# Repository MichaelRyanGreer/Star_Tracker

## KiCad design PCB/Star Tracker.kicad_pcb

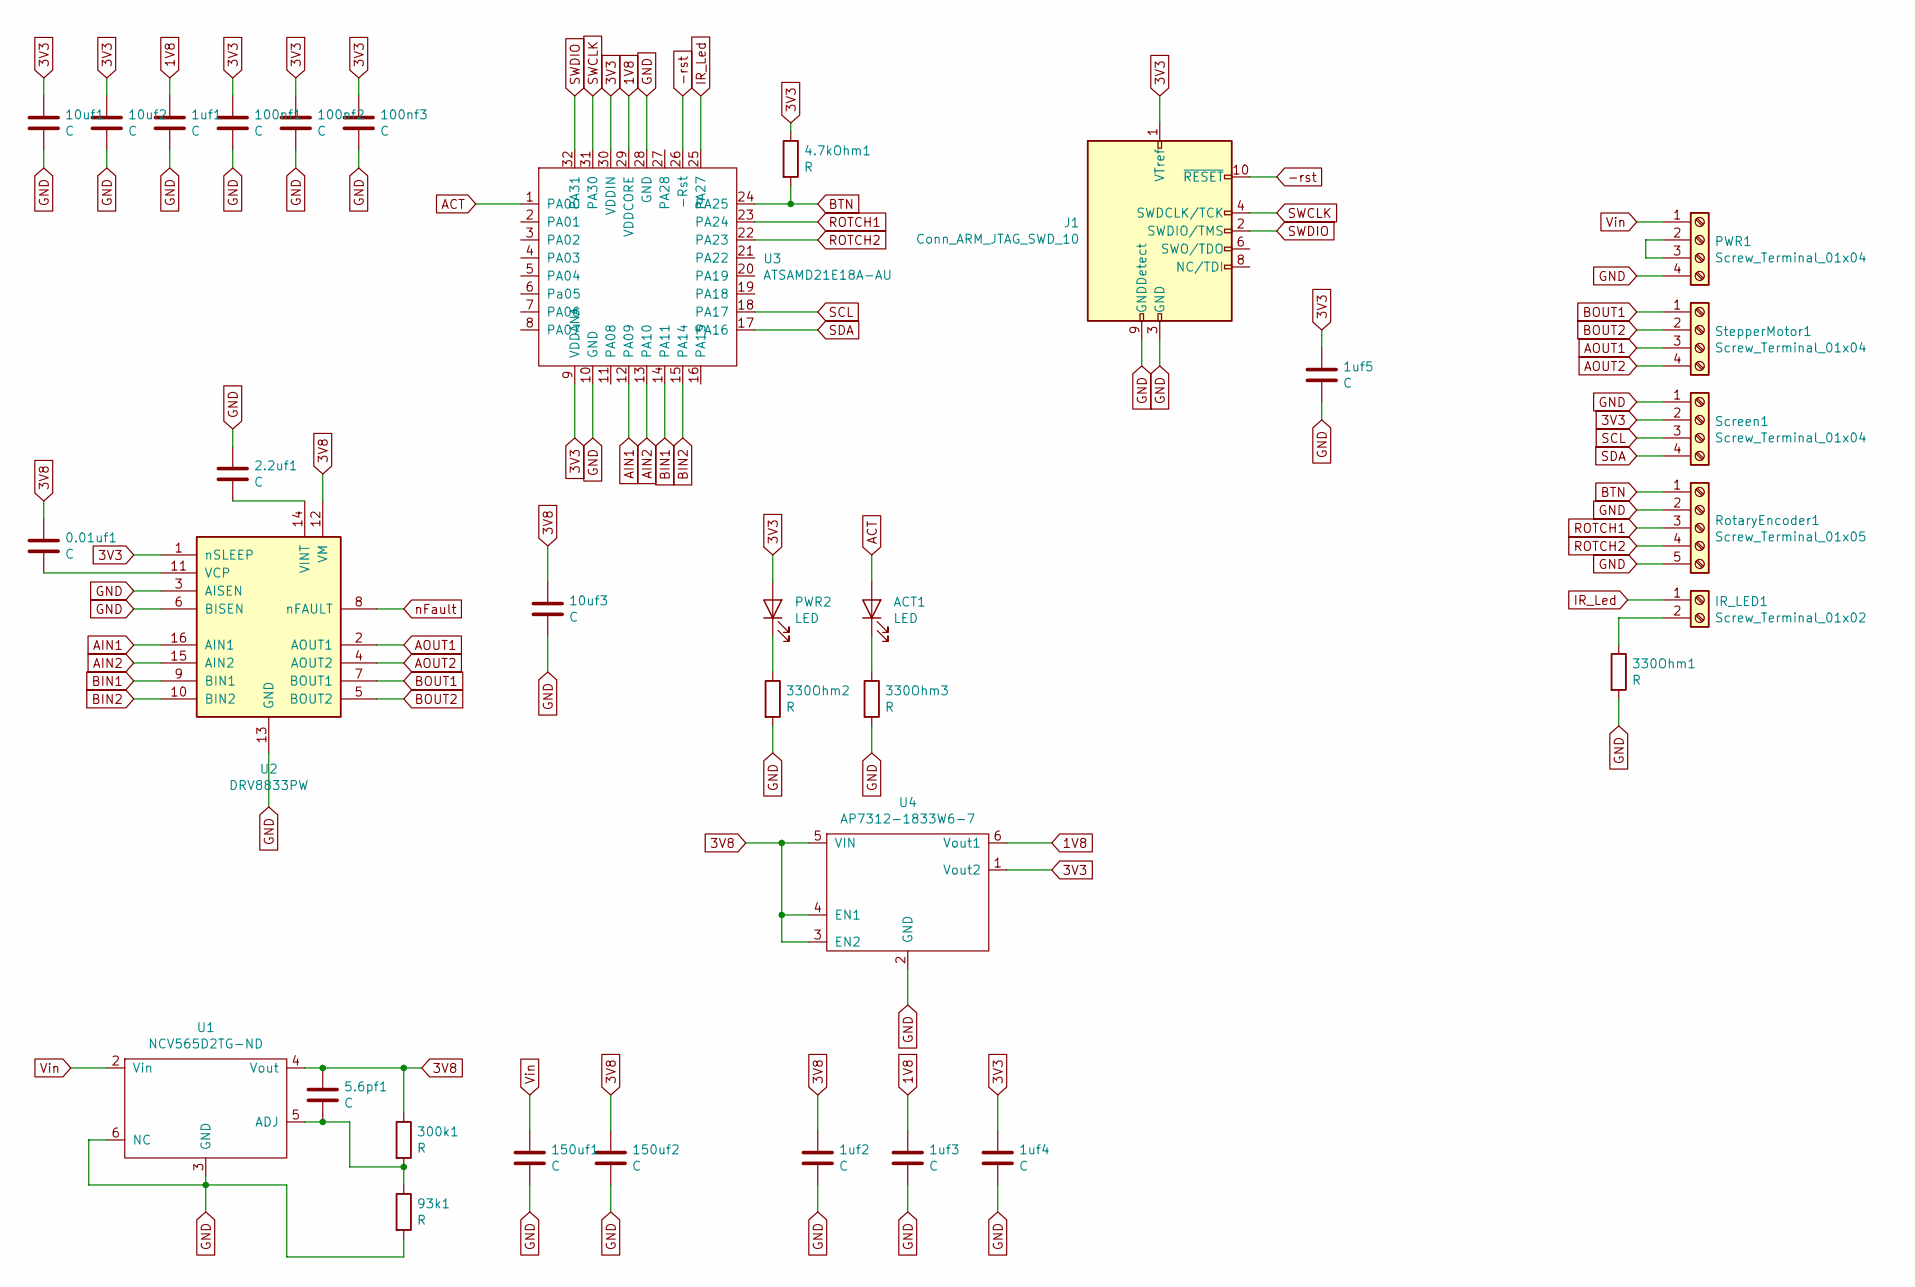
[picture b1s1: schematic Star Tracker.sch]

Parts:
0.01uf1, 1uf1, 1uf2, 1uf3, 1uf4, 1uf5, 2.2uf1, 5.6pf1, 10uf1, 10uf2, 10uf3, 100nf1, 100nf2, 100nf3, 150uf1, 150uf2: C; C_1206_3216Metric_Pad1.42x1.75mm_HandSolder
4.7kOhm1, 93k1, 300k1, 330Ohm1, 330Ohm2, 330Ohm3: R; R_1206_3216Metric_Pad1.42x1.75mm_HandSolder
ACT1: LED; D_1206_3216Metric_Pad1.42x1.75mm_HandSolder
IR_LED1: Screw_Terminal_01x02; PhoenixContact_MC_1,5_2-G-3.5_1x02_P3.50mm_Horizontal
J1: Conn_ARM_JTAG_SWD_10; PinHeader_2x05_P1.27mm_Vertical_SMD
PWR1: Screw_Terminal_01x04; PhoenixContact_MC_1,5_4-G-3.5_1x04_P3.50mm_Horizontal
PWR2: LED; D_1206_3216Metric_Pad1.42x1.75mm_HandSolder
RotaryEncoder1: Screw_Terminal_01x05; PhoenixContact_MC_1,5_5-G-3.5_1x05_P3.50mm_Horizontal
Screen1: Screw_Terminal_01x04; PhoenixContact_MC_1,5_4-G-3.5_1x04_P3.50mm_Horizontal
StepperMotor1: Screw_Terminal_01x04; PhoenixContact_MC_1,5_4-G-3.5_1x04_P3.50mm_Horizontal
U1: NCV565D2TG-ND; TO-263-5_TabPin6
U2: DRV8833PW; TSSOP-16_4.4x5mm_P0.65mm
U3: ATSAMD21E18A-AU; TQFP-32_7x7mm_P0.8mm
U4: AP7312-1833W6-7; SOT-23-6_Handsoldering

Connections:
1V8: 1uf1.1, 1uf3.1, U3.29 (VDDCORE), U4.6 (Vout1)
3V3: 1uf4.1, 1uf5.1, 4.7kOhm1.1, 10uf1.1, 10uf2.1, 100nf1.1, 100nf2.1, 100nf3.1, J1.1 (VTref), PWR2.2 (A), Screen1.2, U2.1 (nSLEEP), U3.9 (VDDANA), U3.30 (VDDIN), U4.1 (Vout2)
3V8: 0.01uf1.1, 1uf2.1, 5.6pf1.1, 10uf3.1, 150uf2.1, 300k1.1, U1.4 (Vout), U2.12 (VM), U4.3 (EN2), U4.4 (EN1), U4.5 (VIN)
-rst: J1.10 (~RESET~), U3.26 (-Rst)
ACT: ACT1.2 (A), U3.1 (PA00)
AIN1: U2.16 (AIN1), U3.12 (PA09)
AIN2: U2.15 (AIN2), U3.13 (PA10)
AOUT1: StepperMotor1.3, U2.2 (AOUT1)
AOUT2: StepperMotor1.4, U2.4 (AOUT2)
BIN1: U2.9 (BIN1), U3.14 (PA11)
BIN2: U2.10 (BIN2), U3.15 (PA14)
BOUT1: StepperMotor1.1, U2.7 (BOUT1)
BOUT2: StepperMotor1.2, U2.5 (BOUT2)
BTN: 4.7kOhm1.2, RotaryEncoder1.1, U3.24 (PA25)
GND: 1uf1.2, 1uf2.2, 1uf3.2, 1uf4.2, 1uf5.2, 2.2uf1.1, 10uf1.2, 10uf2.2, 10uf3.2, 93k1.2, 100nf1.2, 100nf2.2, 100nf3.2, 150uf1.2, 150uf2.2, 330Ohm1.2, 330Ohm2.2, 330Ohm3.2, J1.3 (GND), J1.5 (GND), J1.9 (GNDDetect), PWR1.4, RotaryEncoder1.2, RotaryEncoder1.5, Screen1.1, U1.3 (GND), U1.6 (NC), U2.3 (AISEN), U2.6 (BISEN), U2.13 (GND), U3.10 (GND), U3.28 (GND), U4.2 (GND)
IR_Led: IR_LED1.1, U3.25 (PA27)
unnamed: 0.01uf1.2, U2.11 (VCP)
unnamed: 2.2uf1.2, U2.14 (VINT)
unnamed: 5.6pf1.2, 93k1.1, 300k1.2, U1.5 (ADJ)
unnamed: 330Ohm1.1, IR_LED1.2
unnamed: 330Ohm2.1, PWR2.1 (K)
unnamed: 330Ohm3.1, ACT1.1 (K)
unnamed: PWR1.2, PWR1.3
ROTCH1: RotaryEncoder1.3, U3.23 (PA24)
ROTCH2: RotaryEncoder1.4, U3.22 (PA23)
SCL: Screen1.3, U3.18 (PA17)
SDA: Screen1.4, U3.17 (PA16)
SWCLK: J1.4 (SWDCLK/TCK), U3.31 (PA30)
SWDIO: J1.2 (SWDIO/TMS), U3.32 (PA31)
Vin: 150uf1.1, PWR1.1, U1.2 (Vin)
nFault: U2.8 (nFAULT)

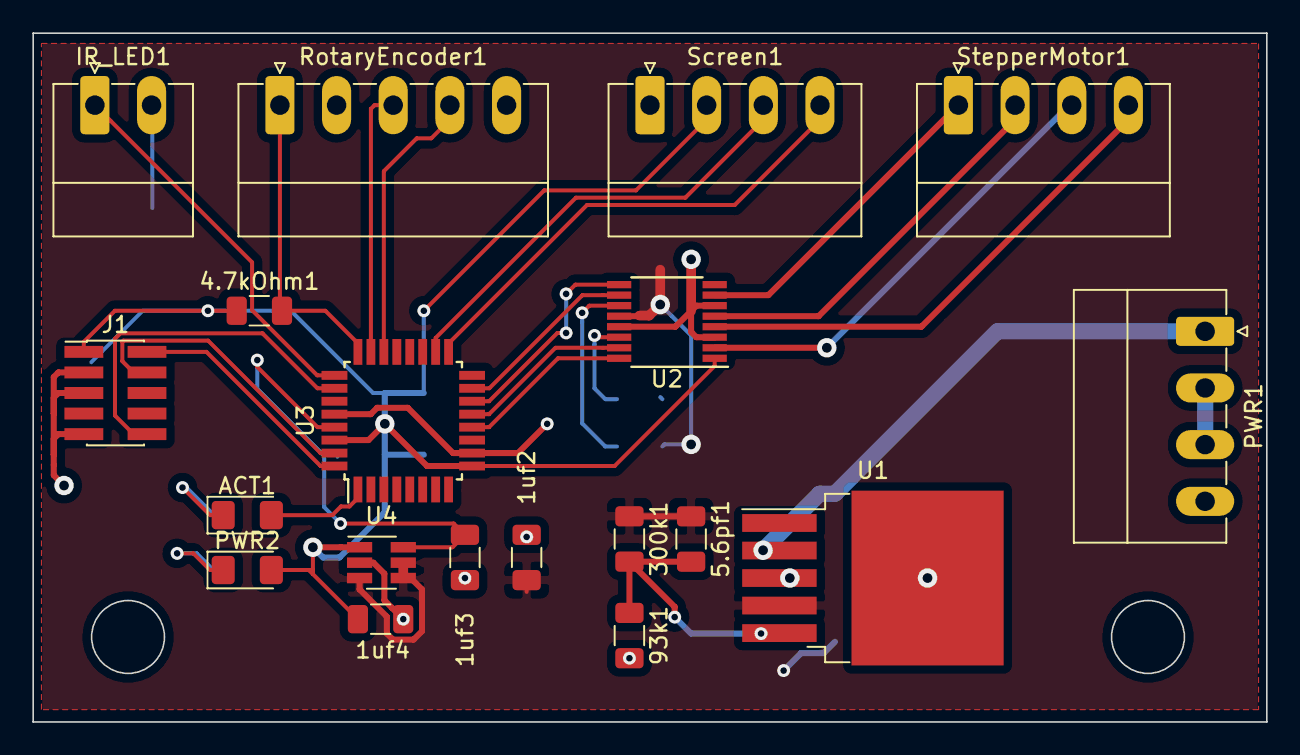
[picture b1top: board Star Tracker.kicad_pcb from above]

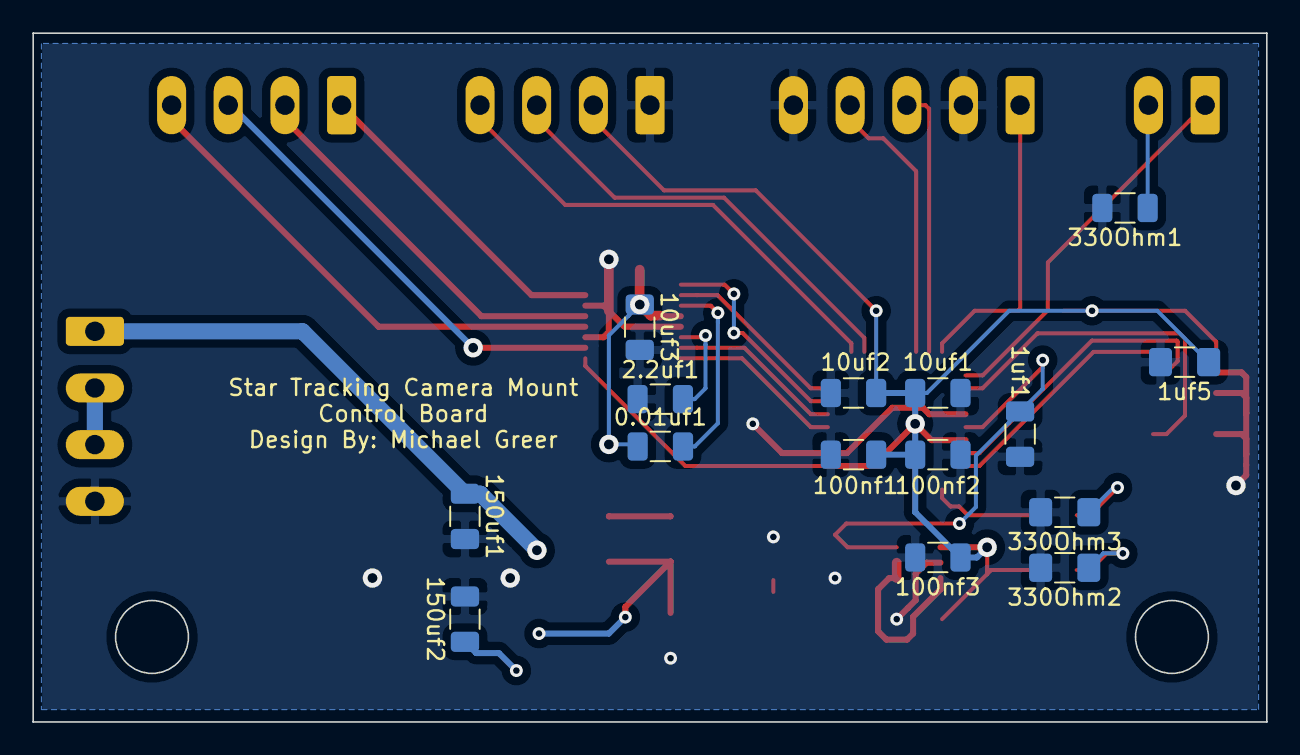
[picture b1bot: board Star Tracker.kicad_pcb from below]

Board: 2 copper layers, 76.2 x 42.5 mm, 34 parts (15 on the bottom side), 30 nets.

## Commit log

2019-09-27 Added status LEDs
2019-10-01 Connected some more screw terminals
2019-10-01 Finished first pass at schematic
2019-10-01 Created PCB
2019-10-02 Fixed broken schematic and started on layout
2019-10-02 Finished layout, minus copper fills
2019-10-03 Finished layout and greated gerbers. Off to fab!
2019-10-23 Added stl files to repo
2019-10-23 Lengthened body
2019-11-08 Swapped 93k and 300k resistors
2019-11-17 Merged motor mount to bottom plate assembly
2019-11-17 Swapped side of motor mount
2019-11-17 Fixed bad stl export
2019-11-20 Widened motor mount and added laser clamp
2019-11-20 Made hole for bearing larger
2019-12-02 Widened roller hole and thinned out motor mount
2019-12-06 Added spacers
2019-12-13 Finished writing control code
